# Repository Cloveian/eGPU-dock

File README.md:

## Goal

Create a single-board Thunderbolt 4 dock with:

* PCIe x4 GPU slot
* M.2 NVMe slot
* Lots of USB Ports
* Fast Ethernet
* 60–100 W Power Delivery (PD)
* Single voltage input

---

## Design Constraints / Features

### Wanted Features

* **Thunderbolt 4 (TB4) connection**

  * One TB4 port dedicated to PCIe tunneling for GPU
  * One TB4 port dedicated to M.2 NVMe, USB, and Ethernet
* **PCIe 4.0 x4 slot**

  * Maximum lanes available over TB4 (for GPU)
* **M.2 NVMe slot**

  * PCIe Gen4 x2
* **Power Delivery (PD)**

  * 60–100 W to laptop over TB4
* **USB Hub**

  * 4 USB-C ports
  * 4 USB-A 3.x ports
* **Single Voltage Input**

  * Powers all components: TB4 controller, USB hub, NVMe, optional GPU rails

---

## Notes / Design Considerations

* **PCIe Lane Allocation**

  * TB4 Port 1: x4 lanes → GPU
  * TB4 Port 2: x4 lanes → M.2 NVMe, USB, and Ethernet
* **Power Distribution**

  * Hub powered from 5 V regulated rail
  * NVMe powered from 3.3 V regulated rail
  * Optional GPU rails from main input if using external connector
* **High-Speed Signal Integrity**

  * Controlled impedance for PCIe and TB4 differential pairs
  * Length matching for PCIe lanes
* **Thermal Management**

  * Heatsink for ASM2464PD TB4 controllers
  * Airflow for GPU and NVMe
  * Optional fan headers
* **User QoL Features**

  * LED indicators: TB4 link, GPU detected, NVMe active, USB hub power/activity
  * Hot-plug detection and optional soft-reset for GPU/NVMe
  * Debug/test points for PCIe, USB lanes, and PD monitoring

---

## Component Selection

| Component                       | Model / Notes                         |
| ------------------------------- | ------------------------------------- |
| TB4 Controller                  | 2x ASM2464PD                          |
| PCIe Fanout Chip (USB+2.5G MAC) | PCI11414C                             |
| 2.5GbE Transceiver              | TBD                                   |
| USB Hub(S)                      | 1x USB7216C + 1x USB7206C             |
| PD+USB-C negotiation            | TBD                                   |
| Voltage Regulators              | Switching / Linear as required        |

<!--
[https://files.slop.gay/pub/docs/Asmedia/ASM2464PD-X/](https://files.slop.gay/pub/docs/Asmedia/ASM2464PD-X/)
-->

---

## Data Flow

---
<!-- 
## Electrical / Power Planning

* Input Voltage: 12–20 V (regulated for all components)
* Power Budget:

  * GPU: external connector
  * NVMe: 3.3 V / 5 V
  * USB hub: 5 V, max 900 mA per USB-A port, PD for USB-C ports
* PD Output: 60–100 W to host laptop
* Overcurrent / overvoltage protection per rail

---
-->

## Mechanical / PCB Planning

#### Layer Stackup
| Layer | Type   | Primary Use                  | Key PI/SI Note                                                      |
|-------|--------|------------------------------|---------------------------------------------------------------------|
| L1    | Signal | HS (TB4, PCIe)               | Microstrip. Route shortest high-speed traces here.                  |
| L2    | GND    | Solid Ground                 | Unified Ground. Primary reference for L1 & L3.                      |
| L3    | Signal | HS (TB4, PCIe)               | Stripline. Route longest critical differential pairs. Ref: L2/L4.   |
| L4    | GND    | Solid Ground                 | Unified Ground. Shields top signals from the power core.            |
| L5    | Signal | HS (USB 3.2, 2.5GbE)         | Stripline. Secondary high-speed routing layer. Ref: L4/L6.          |
| L6    | PWR    | 12V GPU Rail                 | CRITICAL: Use 2 oz copper. Sandwiched by L5 & L7 GND for isolation. |
| L7    | GND    | Solid Ground                 | Unified Ground. Isolates 12V from 5V.                               |
| L8    | PWR    | 5V System Rail               | Sandwiched by L7 & L9 GND. Consider 2 oz copper if current is high. |
| L9    | GND    | Solid Ground                 | Unified Ground. Isolates 5V from 3.3V.                              |
| L10   | PWR    | 3.3V Logic Rail              | Sensitive. Ideal layer for small Analog Power Island split.         |
| L11   | GND    | Solid Ground                 | Unified Ground. Shields core from bottom signals.                   |
| L12   | Signal | LS (I2C, SPI)                | Stripline. Good for noisy low-speed digital signals.                |
| L13   | Signal | LS (GPIOs)                   | Stripline. General-purpose routing.                                 |
| L14   | Signal | LS (Audio)                   | Stripline. Keep sensitive audio traces here.                        |
| L15   | Signal | POL Islands / Spare          | Ideal for local low-voltage power islands (1.050V, 1.900V).         |
| L16   | Signal | Component Breakout           | Microstrip. Used for lower speed/density connections.               |

---
<!--
## Notes / To-Do

* Final PCIe lane allocation plan
* USB hub layout (mix of USB-C / USB-A)
* 3D case design / airflow
* PCB stackup, layer allocation
* Component sourcing & cost analysis
* Firmware testing (hot-plug, soft-reset, PD negotiation)

---
-->

<!--
## References

* ASM2464PD datasheet
* CYUSB3304 datasheet
* TPS65987DDJ datasheet
* PCIe / Thunderbolt routing guides
* Voltage regulator datasheets

---
-->

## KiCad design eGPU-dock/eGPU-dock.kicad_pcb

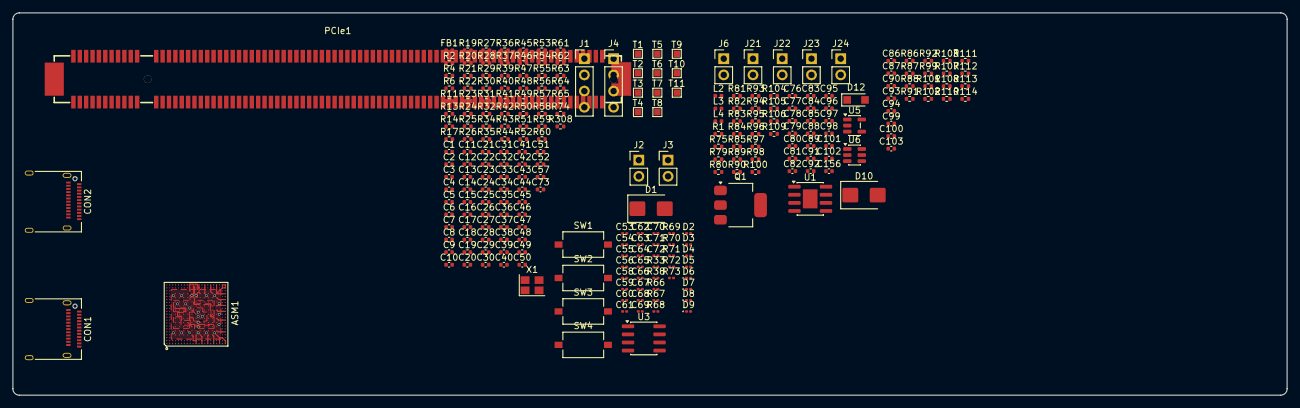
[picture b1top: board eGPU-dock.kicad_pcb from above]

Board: 16 copper layers, 200.0 x 60.0 mm, 253 parts (0 on the bottom side), 145 nets.

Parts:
ASM1: ASM2464PDX
C1, C2, C3, C9, C10, C11, C15, C16, C17, C88, C89: 2.2UF/6.3V; C_0402_1005Metric
C4, C5, C6, C12, C13, C14, C18, C19, C20, C21: 10UF/6.3V; C_0402_1005Metric
C7, C78, C79: 22UF/6.3V; C_0402_1005Metric
C8, C23, C26, C27, C30, C31, C34, C35, C39: 0.22UF/10V; C_0402_1005Metric
C22, C24, C25, C28, C29, C32, C33, C36, C37, C40, C41, C42, C43, C44, C45, C46: 0.22UF/6.3V; C_0402_1005Metric
C38: 10PF/50V; C_0402_1005Metric
C47, C48: 0.22UF/16V; C_0402_1005Metric
C49, C50, C51, C52: 1UF/10V; C_0402_1005Metric
C53, C54: 220PF/50V; C_0201_0603Metric
C55, C56, C58, C59, C60, C61: 0.1UF/25V; C_0201_0603Metric
C57, C73, C81, C82, C84, C85, C92, C101, C156: 0.1UF/16V; C_0402_1005Metric
C62, C63, C64, C65, C69, C70, C71, C72: 0.33UF/25V; C_0201_0603Metric
C66, C67: 0.1UF/16V; C_0201_0603Metric
C68: 1UF/16V; C_0201_0603Metric
C76, C77: 15PF/50V; C_0402_1005Metric
C80, C83: 10UF/16V; C_0402_1005Metric
C86, C87, C90, C93, C94, C99, C100, C103: 0.22u; C_0402_1005Metric
C91: 0.1UF/50V; C_0402_1005Metric
C95, C96: 22UF/10V; C_0402_1005Metric
C97, C98: 10UF/25V; C_0402_1005Metric
C102: 3300PF/50V; C_0402_1005Metric
CON1, CON2: USB_C_Plug; USB_C_Receptacle_Amphenol_12401610E4-2A
D1, D10: SR34; D_SMB
D2, D3, D4, D5, D6, D7, D8, D9: ESD150; D_0201_0603Metric
D12: B130LAW; Nexperia_CFP3_SOD-123W
FB1: 5nF; L_0402_1005Metric
J1, J4: Conn_01x04; PinHeader_1x04_P2.54mm_Vertical
J2, J3, J6, J21, J22, J23, J24: Conn_01x02; PinHeader_1x02_P2.54mm_Vertical
L2, L3: 2.2UH; L_0402_1005Metric
L4: 10UH; L_0402_1005Metric
PCIe1: PCIexpress_x16; CONN-SMD_164P-P1.00_X1611WVS-164-9TV30
Q1: GS1117AXF; SOT-223
R1: 2.2KΩ; R_0402_1005Metric
R2: 20Ω; R_0402_1005Metric
R4, R11, R17, R19, R25, R26, R29, R31, R32, R34, R36, R37, R41, R54, R55, R59, R63, R64, R65, R74, R75, R84, R87, R88, R91, R92, R93, R94, R95, R96, R97, R99, R101, R102, R103, R104, R105, R107, R108, R110, R111, R112, R113, R114, R308: 0Ω; R_0402_1005Metric
R6, R20, R21, R24, R27, R28, R30, R81, R85, R100: 100KΩ; R_0402_1005Metric
R13, R43, R44, R45, R46, R47, R48, R49, R50, R51, R52, R53, R56, R57, R58, R61, R62: 4.7KΩ; R_0402_1005Metric
R14, R22, R23, R35: 1KΩ; R_0402_1005Metric
R33, R38: 0Ω; R_0201_0603Metric
R39, R40: 2MΩ; R_0402_1005Metric
R42: 12.1KΩ; R_0402_1005Metric
R60, R106: 10KΩ; R_0402_1005Metric
R66, R67, R68, R69, R70, R71, R72, R73: 220KΩ; R_0201_0603Metric
R79: 330KΩ; R_0402_1005Metric
R80, R89: 150KΩ; R_0402_1005Metric
R82: 165Ω; R_0402_1005Metric
R83: 100Ω; R_0402_1005Metric
R86: 4.7kΩ; R_0402_1005Metric
R90: 180KΩ; R_0402_1005Metric
R98: 28KΩ; R_0402_1005Metric
R109: 7.5KΩ; R_0402_1005Metric
SW1, SW2, SW3, SW4: SW_Push; SW_Tactile_SPST_NO_Straight_CK_PTS636Sx25SMTRLFS
T1, T2, T3, T4, T5, T6, T7, T8, T9, T10, T11: TestPoint; TestPoint_Pad_1.0x1.0mm
U1: MP2307DN; SOIC-8-1EP_3.9x4.9mm_P1.27mm_EP2.29x3mm
U3: W25X20CLSN; SOIC-8_3.9x4.9mm_P1.27mm
U5: RT8059; TSOT-23-5
U6: ID8225B-ADA60; SOT-23-6
X1: 25 Mhz; Crystal_SMD_Abracon_ABM8AIG-4Pin_3.2x2.5mm

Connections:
3V3OUT_1D: C80.2, C81.2, Q1.2 (OUT), Q1.4 (Vout), R83.1, R84.2
+1.05V_PG: R75.1, U6.5 (PG)
+3.3V: J6.1, R86.1
+3.3V_PCIE: PCIe1.A9 (+3.3V), PCIe1.A10 (+3.3V), PCIe1.B8 (+3.3V)
+5V_BUS: C82.2, C83.2, C88.2, C89.2, D1.1 (K), J2.1, Q1.3 (IN), R54.2, R55.1, R81.1, R85.1, R95.1, U5.4 (VIN), U6.4 (VIN)
+5V_BUS_CON: C55.1, C56.1, C58.1, C59.1, C60.1, C61.1, C66.2, C67.2, CON1.A4 (VBUS), CON1.A9 (VBUS), CON1.B4 (VBUS), CON1.B9 (VBUS), D1.2 (A), J2.2, R54.1, R55.2, R57.2, R94.1
+12V_AD: J23.1, R104.1
+12V_ATX: J23.2, J24.2
+12V_PCIE: PCIe1.A2 (+12V), PCIe1.A3 (+12V), PCIe1.B1 (+12V), PCIe1.B2 (+12V), PCIe1.B3 (+12V)
/GPU/GPU1/CLONE: C50.2, R27.2, R29.1, SW3.1
/GPU/GPU1/ERASE: C49.2, R24.2, R25.1, R26.1, SW1.1
/GPU/GPU1/I2C_INT_PDC: J3.1, R63.1
/GPU/GPU1/I2C_VCC_P: J4.1, R74.1
/GPU/GPU1/VBUS_CON: C68.2, R57.1, R59.2, R60.2
/GPU/GPU2/1V8_EN: C84.2, R85.2, U5.1 (EN)
/GPU/GPU2/+1.05V_EN: C85.2, R81.2, U6.1 (EN)
/GPU/GPU2/FB_1V8: C77.1, R79.2, R89.1, U5.5 (OUT)
/GPU/GPU2/FB_3V3_1D: Q1.1 (ADJ/GND), R82.1, R83.2
/GPU/GPU2/PS_ON#: C156.2, J22.1, R1.2
/GPU/GPU3/PCIe_TX0_C+: C86.2, PCIe1.B14 (PETp0)
/GPU/GPU3/PCIe_TX0_C-: C87.2, PCIe1.B15 (PETn0)
/GPU/GPU3/PCIe_TX1_C+: C90.2, PCIe1.B19 (PETp1)
/GPU/GPU3/PCIe_TX1_C-: C93.2, PCIe1.B20 (PETn1)
/GPU/GPU3/PCIe_TX2_C+: C94.2, PCIe1.B23 (PETp2)
/GPU/GPU3/PCIe_TX2_C-: C99.2, PCIe1.B24 (PETn2)
/GPU/GPU3/PCIe_TX3_C+: C100.2, PCIe1.B27 (PETp3)
/GPU/GPU3/PCIe_TX3_C-: C103.2, PCIe1.B28 (PETn3)
AD2: C95.2, C96.2, D10.2 (A), L4.2, R96.1, R97.1, R98.1
CC1: ASM1.AA6 (CC1), C54.2, R33.1
CC1_C: CON1.A5 (CC), R33.2
CC2: ASM1.Y6 (CC2), C53.2, R38.1
CC2_C: CON1.B5 (VCONN), R38.2
GND: ASM1.AA1 (GNDA), ASM1.AA2 (GNDA), ASM1.AA5 (GNDA), ASM1.AA9 (GNDA), ASM1.AA12 (GNDA), ASM1.AA14 (GNDA), ASM1.AA16 (GNDA), ASM1.AA18 (GNDA), ASM1.AA20 (GNDA), ASM1.AA21 (GNDA), ASM1.D4 (GND), ASM1.D5 (GND), ASM1.D11 (GND), ASM1.D17 (GND), ASM1.D18 (GND), ASM1.E4 (GND), ASM1.E5 (GND), ASM1.E17 (GND), ASM1.E18 (GND), ASM1.F4 (GND), ASM1.F5 (GND), ASM1.F8 (GND), ASM1.F17 (GND), ASM1.F18 (GND), ASM1.H4 (GND), ASM1.H8 (GND), ASM1.H17 (GND), ASM1.H18 (GND), ASM1.J4 (GND), ASM1.J5 (GND), ASM1.J6 (GND), ASM1.J11 (GND), ASM1.K2 (GND), ASM1.L1 (GNDA), ASM1.L2 (GNDA), ASM1.L4 (GNDA), ASM1.L5 (GNDA), ASM1.L9 (GND), ASM1.L13 (GND), ASM1.M20 (GNDA), ASM1.M21 (GNDA), ASM1.N1 (GNDA), ASM1.N2 (GNDA), ASM1.N4 (GNDA), ASM1.N5 (GNDA), ASM1.N9 (GND), ASM1.N11 (GND), ASM1.N13 (GND), ASM1.N17 (GNDA), ASM1.N18 (GNDA), ASM1.P4 (GNDA), ASM1.P5 (GNDA), ASM1.P9 (GND), ASM1.P11 (GND), ASM1.P17 (GNDA), ASM1.P18 (GNDA), ASM1.P20 (GNDA), ASM1.P21 (GNDA), ASM1.R1 (GNDA), ASM1.R2 (GNDA), ASM1.T4 (GNDA), ASM1.T5 (GNDA), ASM1.T17 (GNDA), ASM1.T18 (GNDA), ASM1.T20 (GNDA), ASM1.T21 (GNDA), ASM1.U1 (GNDA), ASM1.U2 (GNDA), ASM1.U4 (GNDA), ASM1.U5 (GNDA), ASM1.U17 (GNDA), ASM1.U18 (GNDA), ASM1.V4 (GNDA), ASM1.V5 (GNDA), ASM1.V6 (GNDA), ASM1.V8 (GNDA), ASM1.V9 (GNDA), ASM1.V11 (GNDA), ASM1.V13 (GNDA), ASM1.V14 (GNDA), ASM1.V16 (GNDA), ASM1.V17 (GNDA), ASM1.V18 (GNDA), ASM1.V20 (GNDA), ASM1.V21 (GNDA), ASM1.W1 (GNDA), ASM1.W2 (GNDA), ASM1.Y3 (GNDA), ASM1.Y5 (GNDA), ASM1.Y9 (GNDA), ASM1.Y12 (GNDA), ASM1.Y14 (GNDA), ASM1.Y16 (GNDA), ASM1.Y18 (GNDA), ASM1.Y20 (GNDA), ASM1.Y21 (GNDA), C1.2, C2.2, C3.2, C4.2, C5.2, C6.2, C7.2, C8.2, C9.2, C10.2, C11.2, C12.2, C13.2, C14.2, C15.2, C16.2, C17.2, C18.2, C19.2, C20.2, C21.1, C22.2, C23.2, C24.2, C25.2, C26.2, C27.2, C28.2, C29.2, C30.2, C31.2, C32.2, C33.2, C34.2, C35.2, C36.2, C37.2, C39.2, C40.2, C41.2, C42.2, C43.2, C44.2, C45.2, C46.2, C47.1, C48.1, C49.1, C50.1, C51.1, C52.1, C53.1, C54.1, C55.2, C56.2, C57.1, C58.2, C59.2, C60.2, C61.2, C66.1, C67.1, C68.1, C73.1, C76.1, C78.1, C79.1, C80.1, C81.1, C82.1, C83.1, C84.1, C85.1, C88.1, C89.1, C92.2, C95.1, C96.1, C97.1, C98.1, C101.1, C156.1, CON1.A1 (GND), CON1.A12 (GND), CON1.B1 (GND), CON1.B12 (GND), D2.2 (A2), D3.2 (A2), D4.2 (A2), D5.2 (A2), D6.2 (A2), D7.2 (A2), D8.2 (A2), D9.2 (A2), D12.2 (A), FB1.2, J1.2, J3.2, J4.2, J22.2, PCIe1.A4 (GND), PCIe1.A12 (GND), PCIe1.A15 (GND), PCIe1.A18 (GND), PCIe1.A20 (GND), PCIe1.A23 (GND), PCIe1.A24 (GND), PCIe1.A27 (GND), PCIe1.A28 (GND), PCIe1.A31 (GND), PCIe1.A34 (GND), PCIe1.A37 (GND), PCIe1.A38 (GND), PCIe1.A41 (GND), PCIe1.A42 (GND), PCIe1.A45 (GND), PCIe1.A46 (GND), PCIe1.A49 (GND), PCIe1.A51 (GND), PCIe1.A54 (GND), PCIe1.A55 (GND), PCIe1.A58 (GND), PCIe1.A59 (GND), PCIe1.A62 (GND), PCIe1.A63 (GND), PCIe1.A66 (GND), PCIe1.A67 (GND), PCIe1.A70 (GND), PCIe1.A71 (GND), PCIe1.A74 (GND), PCIe1.A75 (GND), PCIe1.A78 (GND), PCIe1.A79 (GND), PCIe1.A82 (GND), PCIe1.B4 (GND), PCIe1.B7 (GND), PCIe1.B13 (GND), PCIe1.B16 (GND), PCIe1.B18 (GND), PCIe1.B21 (GND), PCIe1.B22 (GND), PCIe1.B25 (GND), PCIe1.B26 (GND), PCIe1.B29 (GND), PCIe1.B32 (GND), PCIe1.B35 (GND), PCIe1.B36 (GND), PCIe1.B39 (GND), PCIe1.B40 (GND), PCIe1.B43 (GND), PCIe1.B44 (GND), PCIe1.B47 (GND), PCIe1.B49 (GND), PCIe1.B52 (GND), PCIe1.B53 (GND), PCIe1.B56 (GND), PCIe1.B57 (GND), PCIe1.B60 (GND), PCIe1.B61 (GND), PCIe1.B64 (GND), PCIe1.B65 (GND), PCIe1.B68 (GND), PCIe1.B69 (GND), PCIe1.B72 (GND), PCIe1.B73 (GND), PCIe1.B76 (GND), PCIe1.B77 (GND), PCIe1.B80 (GND), R2.1, R13.2, R14.2, R22.2, R23.2, R35.2, R39.1, R40.2, R42.1, R45.2, R46.2, R47.2, R48.2, R49.2, R50.2, R51.2, R52.2, R53.2, R56.2, R58.2, R60.1, R66.1, R67.1, R68.1, R69.1, R70.1, R71.1, R72.1, R73.1, R82.2, R89.2, R90.2, R99.1, R105.2, R106.2, R109.1, SW1.2, SW2.2, SW3.2, SW4.2, U1.4 (GND1), U1.9 (GND2), U3.4 (GND), U5.2 (GND), U6.2 (GND), X1.2, X1.4
GPIO0: ASM1.D1 (NVMeACTLED1/GPIO0), R17.2
GPIO1: ASM1.C1 (I2C_INT/GPIO1), R63.2
GPIO2: ASM1.B1 (PRSNT#/GPIO2), R25.2
GPIO3: ASM1.A1 (NVMeACTLED2/GPIO3), C51.2, R19.2, R28.2, SW4.1
GPIO14: ASM1.A20 (CLKREQ1#/GPIO14), R45.1, T4.1
GPIO19: ASM1.A10 (PRSNT1#/GPIO19), R47.1, T5.1
GPIO20: ASM1.A11 (HDDPC1/GPIO20), R49.1, T6.1
GPIO21: ASM1.A12 (PRSNT2#/GPIO21), R51.1, T7.1
GPIO22: ASM1.A13 (PE_WAKE#/GPIO22), R29.2, R52.1
GPIO23: ASM1.A14 (CLKREQ2#/GPIO23), R53.1, T9.1
GPIO24: ASM1.A15 (CLKREQ3#/GPIO24), R56.1, T10.1
GPIO27: ASM1.A18 (PRSNT3#/GPIO27), R26.2, R58.1, T11.1
HDDPC: ASM1.C21 (HDDPC), R11.2, R13.1
HDDPC_C: C21.2, R6.2, R11.1, R14.1, R93.2
I2C_CLK_P1: J4.4, R65.1
I2C_CLK_PD: ASM1.E1 (I2C_CLK_P), R65.2
I2C_DATA_P1: J4.3, R64.1
I2C_DATA_PD: ASM1.F1 (I2C_DATA_P), R64.2
unnamed: C57.2, R41.1
unnamed: C102.1, R109.2
unnamed: CON1.S1 (SHIELD), FB1.1, R2.2
unnamed: D10.1 (K), J6.2, R96.2, R97.2
unnamed: C91.1, D12.1 (K), L4.1, U1.3 (SW)
unnamed: J1.1, R34.1
unnamed: PCIe1.A17 (PERn0), R108.1
unnamed: PCIe1.A22 (PERn1), R101.1
unnamed: PCIe1.A26 (PERn2), R112.1
unnamed: PCIe1.A30 (PERn3), R114.1
unnamed: PCIe1.A16 (PERp0), R107.1
unnamed: PCIe1.A21 (PERp1), R110.1
unnamed: PCIe1.A25 (PERp2), R111.1
unnamed: PCIe1.A29 (PERp3), R113.1
unnamed: PCIe1.A13 (REFCLK+), R102.1
unnamed: PCIe1.A14 (REFCLK-), R103.1
unnamed: PCIe1.B5 (SMCLK), R88.2
unnamed: PCIe1.B6 (SMDAT), R91.2
unnamed: PCIe1.B17 (~PRSNT2), R86.2, R87.2
unnamed: PCIe1.B11 (~WAKE), R92.2
unnamed: C91.2, U1.1 (BS)
unnamed: C101.2, C102.2, U1.6 (COMP)
unnamed: R93.1, R100.2, R105.1, U1.7 (EN)
unnamed: R98.2, R106.1, U1.5 (FB)
unnamed: C97.2, C98.2, R94.2, R95.2, R104.2, U1.2 (IN)
unnamed: C92.1, U1.8 (SS)
unnamed: R62.2, U3.7 (~HOLD)
unnamed: R61.1, U3.3 (~WP)
unnamed: L2.1, U5.3 (SW)
unnamed: R80.2, R90.1, U6.6 (FB)
unnamed: L3.1, U6.3 (SW)
PCIe_PRSNT1: PCIe1.A1 (~PRSNT1), R99.2
PERST_B: ASM1.G21 (PERST0#), C47.2, R20.2, R22.1
PERST_B1: ASM1.F21 (NC/PERST1#), T1.1
PERST_B2: ASM1.E21 (NC/PERST2#), C48.2, R21.2, R23.1
PERST_B3: ASM1.D21 (NC/PERST3#), T2.1
PRX0+: ASM1.N21 (PRXP0), R107.2
PRX0-: ASM1.N20 (PRXN0), R108.2
PRX1+: ASM1.W21 (PRXP1), R110.2
PRX1-: ASM1.W20 (PRXN1), R101.2
PRX2+: ASM1.Y19 (PRXP2), R111.2
PRX2-: ASM1.AA19 (PRXN2), R112.2
PRX3+: ASM1.AA13 (PRXP3), R113.2
PRX3-: ASM1.Y13 (PRXN3), R114.2
PTX0+: ASM1.R20 (PTXP0), C86.1
PTX0-: ASM1.R21 (PTXN0), C87.1
PTX1+: ASM1.U20 (PTXP1), C90.1
PTX1-: ASM1.U21 (PTXN1), C93.1
PTX2+: ASM1.Y17 (PTXP2), C94.1
PTX2-: ASM1.AA17 (PTXN2), C99.1
PTX3+: ASM1.Y15 (PTXP3), C100.1
PTX3-: ASM1.AA15 (PTXN3), C103.1
REFCLK0+: ASM1.AA8 (REFCLKP0), R102.2
REFCLK0-: ASM1.Y8 (REFCLKN0), R103.2
RST: ASM1.H1 (RST#), C52.2, R30.2, R35.1, R75.2, SW2.1
SBU1: ASM1.K1 (SBU1), R36.1
SBU1_C: CON1.A8 (SBU1), R36.2, R40.1
SBU2: ASM1.J1 (SBU2), R37.2
SBU2_C: CON1.B8 (SBU2), R37.1, R39.2
SPI_CLK: ASM1.A5 (GPIO6/SPI_CLK), U3.6 (CLK)
SPI_CS#: ASM1.A2 (GPIO4/SPI_CS#), U3.1 (~CS)
SPI_DI: ASM1.A4 (GPIO7/SPI_DI), U3.5 (DI/IO_{0})
SPI_DO: ASM1.A3 (GPIO5/SPI_DO), R43.1, R48.1, U3.2 (DO/IO_{1})
TEST_EN: ASM1.H21 (TEST_EN), R50.1
UART_RX: ASM1.A21 (PRSNT0#/UART_RX), J1.4, R308.2, T3.1
UART_TX: ASM1.B21 (MEMREPAIR/UART_TX), J1.3, R41.2, R44.1, R46.1
UD+: ASM1.M1 (UDP), R31.1
UD+_C: CON1.A6 (D+), R31.2
UD-: ASM1.M2 (UDM), R32.2
UD-_C: CON1.A7 (D-), R32.1
UREXT: ASM1.AA3 (REXT), R42.2
URX0+: ASM1.P1 (URXP0), C62.1
URX0+_CON: C62.2, CON1.B10 (RX1-), D7.1 (A1), R71.2
URX0-: ASM1.P2 (URXN0), C63.1
URX0-_CON: C63.2, CON1.B11 (RX1+), D9.1 (A1), R73.2
URX1+: ASM1.Y2 (URXP1), C64.1
URX1+_CON: C64.2, CON1.A10 (RX2-), D6.1 (A1), R70.2
URX1-: ASM1.Y1 (URXN1), C65.1
URX1-_CON: C65.2, CON1.A11 (RX2+), D8.1 (A1), R72.2
UTX0+: ASM1.T1 (UTXP0), C69.1
UTX0+_CON: C69.2, CON1.A3 (TX1-), D3.1 (A1), R67.2
UTX0-: ASM1.T2 (UTXN0), C70.1
UTX0-_CON: C70.2, CON1.A2 (TX1+), D5.1 (A1), R69.2
UTX1+: ASM1.V2 (UTXP1), C71.1
UTX1+_CON: C71.2, CON1.B3 (TX2-), D2.1 (A1), R66.2
UTX1-: ASM1.V1 (UTXN1), C72.1
UTX1-_CON: C72.2, CON1.B2 (TX2+), D4.1 (A1), R68.2
VBUS: ASM1.G1 (VBUS), R59.1
VCC18: ASM1.L6 (VCCL), ASM1.L16 (VCCL), ASM1.L17 (VCCL), ASM1.L18 (VCCL), ASM1.L20 (VCCL), ASM1.L21 (VCCL), ASM1.N6 (VCCL), ASM1.N16 (VCCL), ASM1.P6 (VCCL), ASM1.P16 (VCCL), ASM1.T6 (VCCL), ASM1.T16 (VCCL), ASM1.U6 (VCCL), ASM1.U11 (VCCL), ASM1.U13 (VCCL), ASM1.U14 (VCCL), ASM1.U16 (VCCL), C2.1, C5.1, C10.1, C13.1, C17.1, C20.1, C25.1, C29.1, C33.1, C37.1, C41.1, C43.1, C45.1, C46.1, C77.2, C78.2, L2.2, R79.1
VCC33_SYS: ASM1.D6 (VCCH), ASM1.D8 (VCCH), ASM1.D9 (VCCH), ASM1.D13 (VCCH), ASM1.E6 (VCCH), ASM1.E8 (VCCH), ASM1.E9 (VCCH), ASM1.E13 (VCCH), ASM1.F6 (VCCH), ASM1.F13 (VCCH), ASM1.H6 (VCCH), C3.1, C6.1, C11.1, C14.1, C16.1, C19.1, C23.1, C27.1, C31.1, C35.1, C73.2, J21.2, R4.2, R6.1, R20.1, R21.1, R24.1, R27.1, R28.1, R30.1, R34.2, R43.2, R44.2, R61.2, R62.1, R74.2, R84.1, R100.1, U3.8 (VCC)
VCCA33: ASM1.H5 (VCCA33), C7.1, C8.1, R4.1
VDD095: ASM1.D14 (VDD), ASM1.D16 (VDD), ASM1.E11 (VDD), ASM1.E14 (VDD), ASM1.E16 (VDD), ASM1.F9 (VDD), ASM1.F11 (VDD), ASM1.F14 (VDD), ASM1.F16 (VDD), ASM1.H9 (VDD), ASM1.H11 (VDD), ASM1.H13 (VDD), ASM1.H14 (VDD), ASM1.H16 (VDD), ASM1.J8 (VDD), ASM1.J9 (VDD), ASM1.J13 (VDD), ASM1.J14 (VDD), ASM1.J16 (VDD), ASM1.J17 (VDD), ASM1.J18 (VDD), ASM1.J20 (VDD), ASM1.J21 (VDD), ASM1.K20 (VDD), ASM1.K21 (VDD), ASM1.L8 (VDD), ASM1.L11 (VDD), ASM1.L14 (VDD), ASM1.N8 (VDD), ASM1.N14 (VDD), ASM1.P8 (VDD), ASM1.P13 (VDD), ASM1.P14 (VDD), ASM1.T8 (VDD), ASM1.T9 (VDD), ASM1.T11 (VDD), ASM1.T13 (VDD), ASM1.T14 (VDD), ASM1.U8 (VDD), ASM1.U9 (VDD), C1.1, C4.1, C9.1, C12.1, C15.1, C18.1, C22.1, C24.1, C26.1, C28.1, C30.1, C32.1, C34.1, C36.1, C39.1, C40.1, C42.1, C44.1, C76.2, C79.2, L3.2, R80.1
XI: C38.2, X1.3
XO: ASM1.Y4 (XO), C38.1, X1.1

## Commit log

2025-11-18 Revise component selection in README
    Updated component details in the README.
2025-11-18 kicad files
2025-11-19 update kicad
2025-11-20 add footprint+datasheets
2025-11-20 fix symbol
2025-11-20 finish symbol and footprint
2025-11-21 add diagram and stuff
2025-11-21 stuff
2025-11-25 clean up
2025-11-25 fix readme image embbed
2025-11-27 masive schamatic update
2025-11-28 almost as masive schematic update
